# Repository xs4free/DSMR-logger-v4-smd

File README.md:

# DSMR-logger-v4.5

Reverse enginered version of [Willem aan de Wiel](https://github.com/mrWheel)'s excellent [DSMR-logger version 4.5](https://opencircuit.nl/Product/Slimme-meter-uitlezer-V4.5-Geassembleerd) to fit certain components I had lying around. The latest details he published are of the 4.0 version, detailed in [this blog](https://willem.aandewiel.nl/index.php/2019/04/09/dsmr-logger-v4-slimme-meter-uitlezer/).

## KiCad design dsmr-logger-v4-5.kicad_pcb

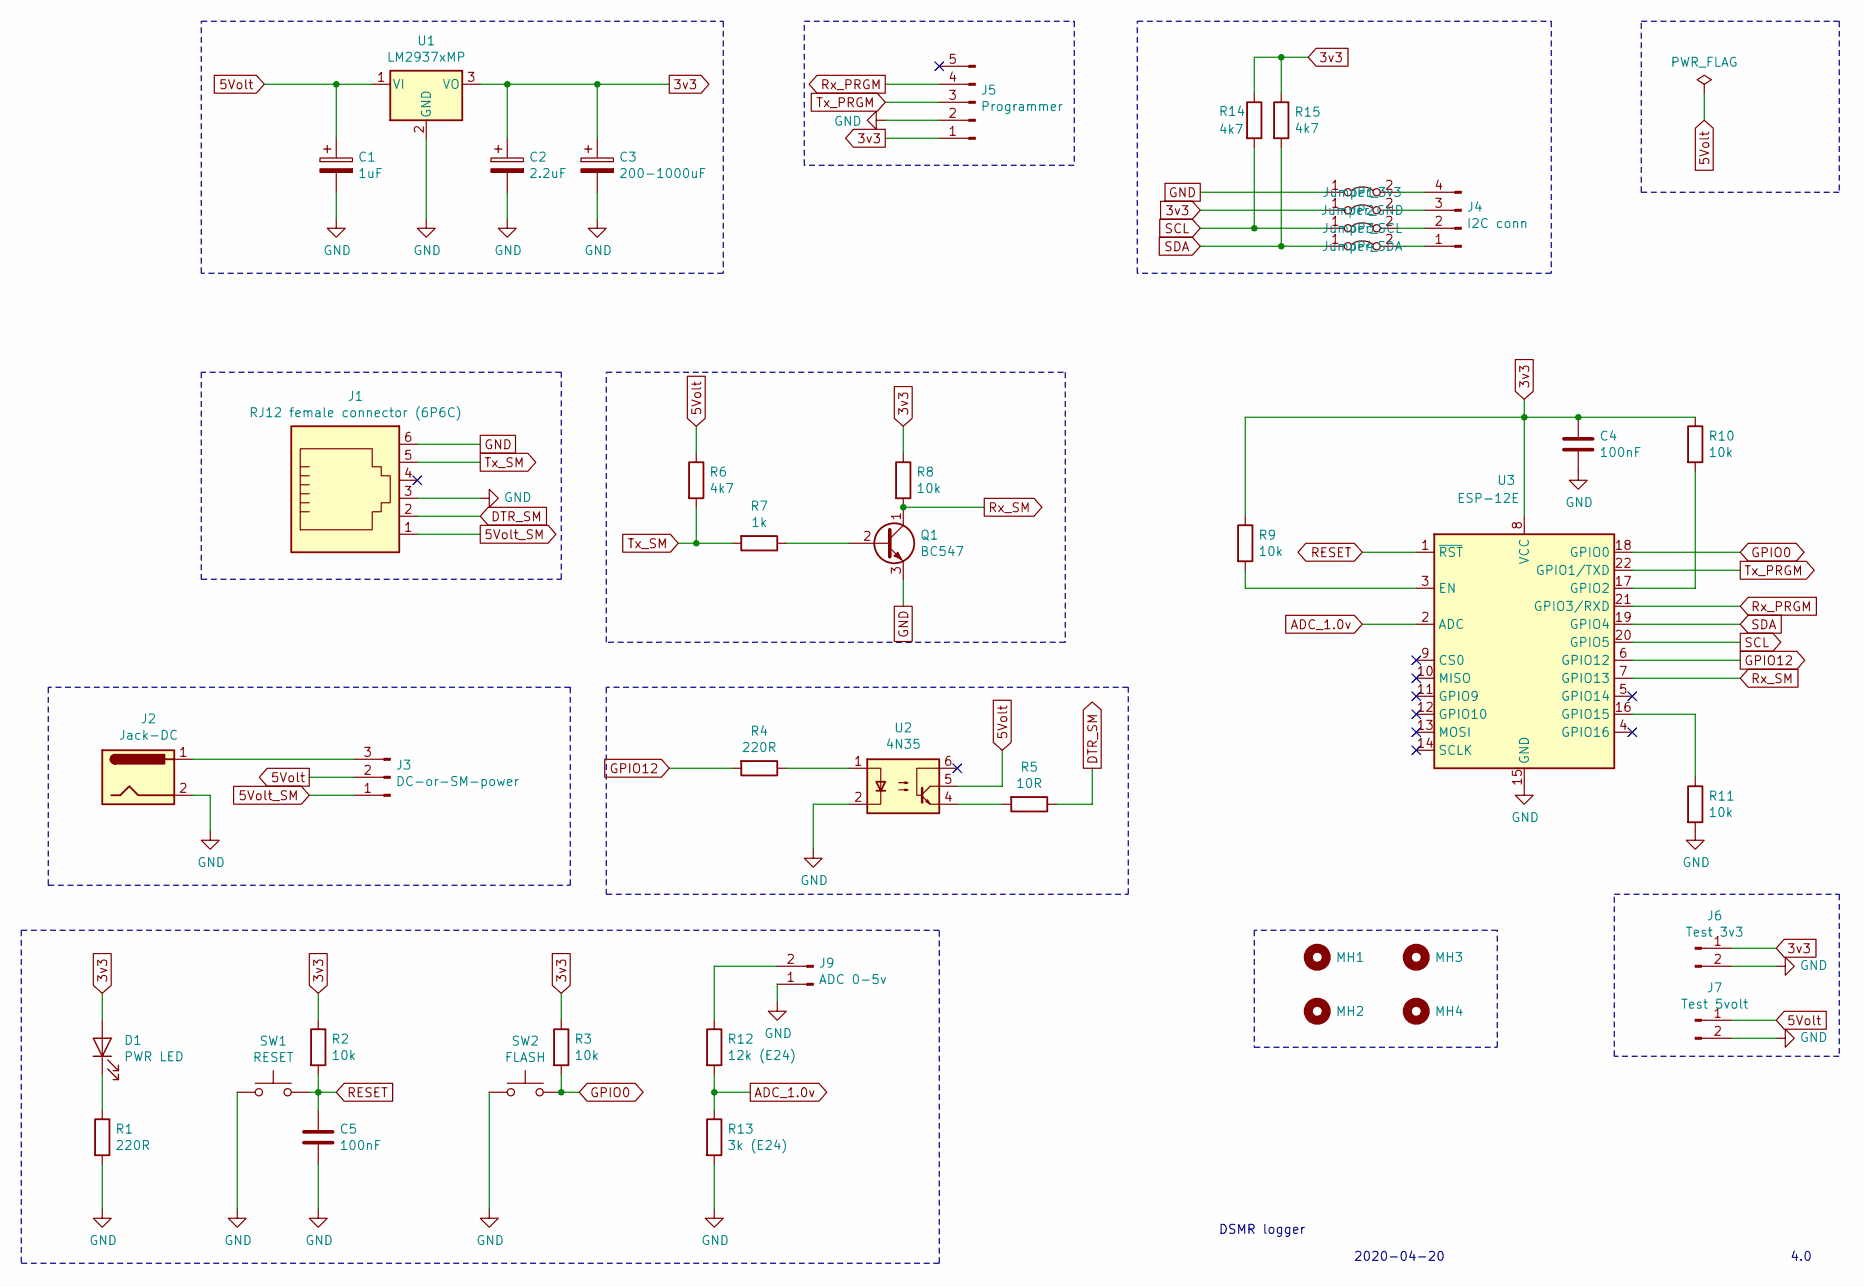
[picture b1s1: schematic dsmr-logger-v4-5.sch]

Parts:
C1: 1uF; CP_Radial_D5.0mm_P2.00mm
C2: 2.2uF; CP_Radial_D5.0mm_P2.00mm
C3: 200-1000uF; CP_Radial_D8.0mm_P5.00mm
C4, C5: 100nF; C_Disc_D5.0mm_W2.5mm_P5.00mm
D1: PWR LED; LED_D3.0mm
J1: RJ12 female connector (6P6C); RJ11-6
J2: Jack-DC; BarrelJack_CUI_PJ-102AH_Horizontal
J3: DC-or-SM-power; PinHeader_1x03_P2.54mm_Vertical
J4: I2C conn; PinSocket_1x04_P2.54mm_Vertical
J5: Programmer; PinHeader_1x05_P2.54mm_Vertical
J6: Test 3v3; PinHeader_1x02_P2.54mm_Vertical
J7: Test 5volt; PinHeader_1x02_P2.54mm_Vertical
J9: ADC 0-5v; PinHeader_1x02_P2.54mm_Vertical
JP1: Jumper_3v3; SolderJumper-2_P1.3mm_Bridged_Pad1.0x1.5mm
JP2: Jumper_GND; SolderJumper-2_P1.3mm_Bridged_Pad1.0x1.5mm
JP3: Jumper_SCL; SolderJumper-2_P1.3mm_Bridged_Pad1.0x1.5mm
JP4: Jumper_SDA; SolderJumper-2_P1.3mm_Bridged_Pad1.0x1.5mm
MH1, MH2, MH3, MH4: MountingHole; MountingHole_2.7mm_M2.5_DIN965
Q1: BC547; TO-92
R1, R4: 220R; R_Axial_DIN0207_L6.3mm_D2.5mm_P7.62mm_Horizontal
R2, R3, R8, R9, R10, R11: 10k; R_Axial_DIN0207_L6.3mm_D2.5mm_P7.62mm_Horizontal
R5: 10R; R_Axial_DIN0207_L6.3mm_D2.5mm_P7.62mm_Horizontal
R6, R14, R15: 4k7; R_Axial_DIN0207_L6.3mm_D2.5mm_P7.62mm_Horizontal
R7: 1k; R_Axial_DIN0207_L6.3mm_D2.5mm_P7.62mm_Horizontal
R12: 12k (E24); R_Axial_DIN0207_L6.3mm_D2.5mm_P7.62mm_Horizontal
R13: 3k (E24); R_Axial_DIN0207_L6.3mm_D2.5mm_P7.62mm_Horizontal
SW1: RESET; SW_PUSH_6mm_H7.3mm
SW2: FLASH; SW_PUSH_6mm_H13mm
U1: LM2937xMP; SOT-223-3_TabPin2
U2: 4N35; DIP-6_W7.62mm
U3: ESP-12E

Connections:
3v3: C2.1, C3.1, C4.1, D1.2 (A), J5.1, J6.1, JP2.1 (A), R2.1, R3.1, R8.1, R9.1, R10.1, R14.1, R15.1, U1.3 (VO), U3.8 (VCC)
5Volt: C1.1, J3.2, J7.1, R6.1, U1.1 (VI), U2.5
5Volt_SM: J1.1, J3.1
ADC_1.0v: R12.2, R13.1, U3.2 (ADC)
DTR_SM: J1.2, R5.1
GND: C1.2, C2.2, C3.2, C4.2, C5.2, J1.3, J1.6, J2.2, J5.2, J6.2, J7.2, J9.1, JP1.1 (A), Q1.3 (E), R1.2, R11.2, R13.2, SW1.1, SW2.1, U1.2 (GND), U2.2, U3.15 (GND)
GPIO0: R3.2, SW2.2, U3.18 (GPIO0)
GPIO12: R4.2, U3.6 (GPIO12)
unnamed: D1.1 (K), R1.1
unnamed: J2.1, J3.3
unnamed: J4.1, JP4.2 (B)
unnamed: J4.2, JP3.2 (B)
unnamed: J4.3, JP2.2 (B)
unnamed: J4.4, JP1.2 (B)
unnamed: J9.2, R12.1
unnamed: Q1.2 (B), R7.1
unnamed: R4.1, U2.1
unnamed: R5.2, U2.4
unnamed: R9.2, U3.3 (EN)
unnamed: R10.2, U3.17 (GPIO2)
unnamed: R11.1, U3.16 (GPIO15)
RESET: C5.1, R2.2, SW1.2, U3.1 (~RST)
Rx_PRGM: J5.4, U3.21 (GPIO3/RXD)
Rx_SM: Q1.1 (C), R8.2, U3.7 (GPIO13)
SCL: JP3.1 (A), R14.2, U3.20 (GPIO5)
SDA: JP4.1 (A), R15.2, U3.19 (GPIO4)
Tx_PRGM: J5.3, U3.22 (GPIO1/TXD)
Tx_SM: J1.5, R6.2, R7.2

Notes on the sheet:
DSMR logger
4.0
2020-04-20

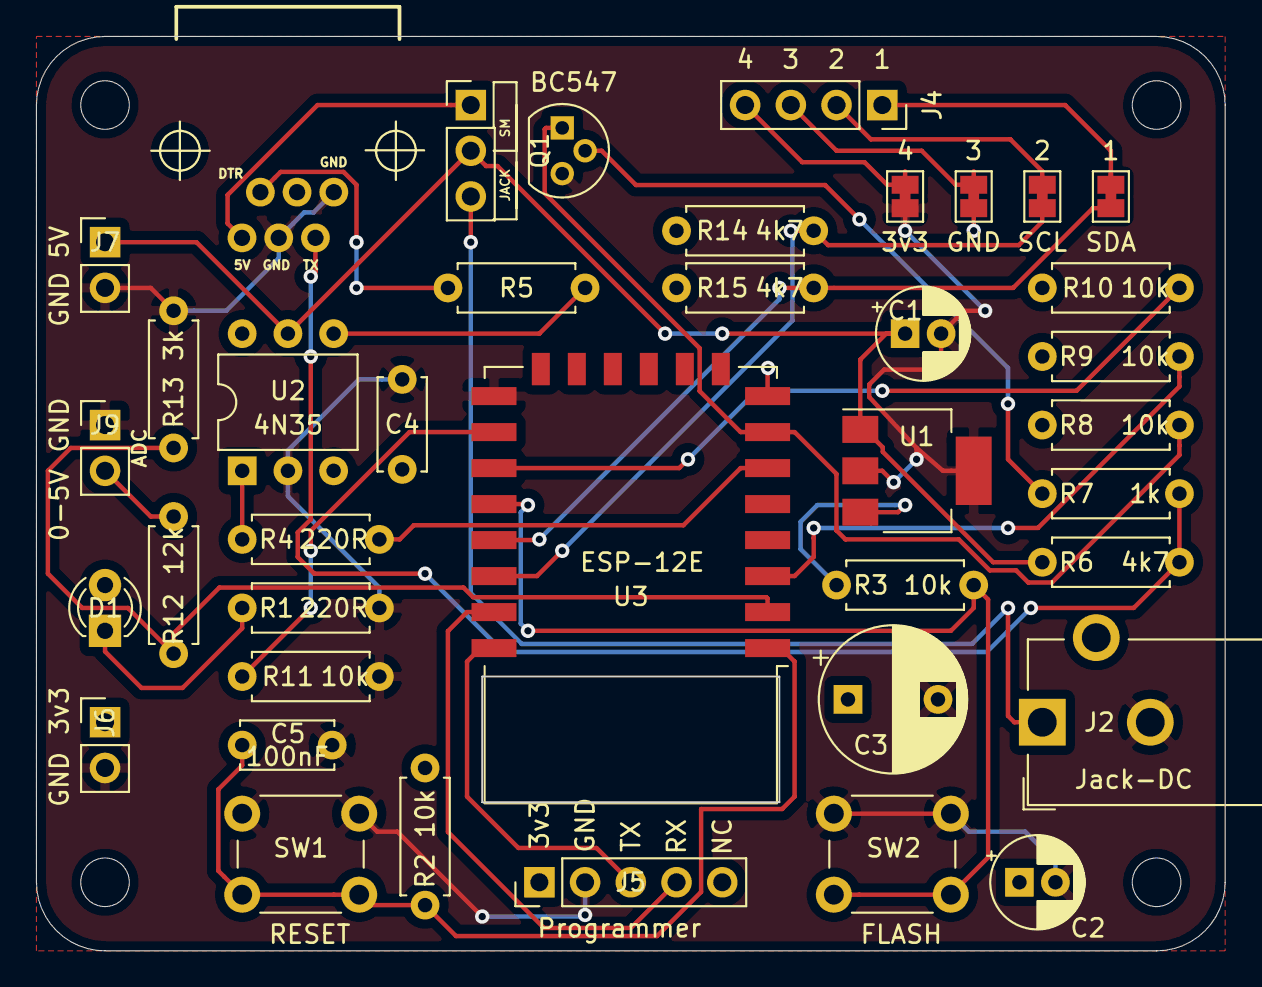
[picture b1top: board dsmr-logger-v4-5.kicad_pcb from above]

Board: 2 copper layers, 66.0 x 50.8 mm, 43 parts (0 on the bottom side), 28 nets.

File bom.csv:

"Source:"	"C:\Git\DSMR-logger-v4-smd\dsmr-logger-v4-5.sch"
"Date:"	"4/20/2020 11:20:06 PM"
"Tool:"	"Eeschema (5.1.5)-3"
"Component Count:"	"43"
"Ref"	"Value"	"Part"	"Footprint"	"Description"	"Vendor"
"C1"	"1uF"	"Device:CP"	"Capacitor_THT:CP_Radial_D5.0mm_P2.00mm"	"Polarized capacitor"	""
"C2"	"2.2uF"	"Device:CP"	"Capacitor_THT:CP_Radial_D5.0mm_P2.00mm"	"Polarized capacitor"	""
"C3"	"200-1000uF"	"Device:CP"	"Capacitor_THT:CP_Radial_D8.0mm_P5.00mm"	"Polarized capacitor"	""
"C4"	"100nF"	"Device:C"	"Capacitor_THT:C_Disc_D5.0mm_W2.5mm_P5.00mm"	"Unpolarized capacitor"	""
"C5"	"100nF"	"Device:C"	"Capacitor_THT:C_Disc_D5.0mm_W2.5mm_P5.00mm"	"Unpolarized capacitor"	""
"D1"	"PWR LED"	"Device:LED"	"LED_THT:LED_D3.0mm"	"Light emitting diode"	""
"J1"	"RJ12 female connector (6P6C)"	"Connector:6P6C"	"Connectors-P1:RJ11-6"	"RJ connector, 6P6C (6 positions 6 connected), RJ12/RJ18/RJ25"	""
"J2"	"Jack-DC"	"Connector:Jack-DC"	"Connector_BarrelJack:BarrelJack_CUI_PJ-102AH_Horizontal"	"DC Barrel Jack"	""
"J3"	"DC-or-SM-power"	"Connector:Conn_01x03_Male"	"Connector_PinHeader_2.54mm:PinHeader_1x03_P2.54mm_Vertical"	"Generic connector, single row, 01x03, script generated (kicad-library-utils/schlib/autogen/connector/)"	""
"J4"	"I2C conn"	"Connector:Conn_01x04_Male"	"Connector_PinSocket_2.54mm:PinSocket_1x04_P2.54mm_Vertical"	"Generic connector, single row, 01x04, script generated (kicad-library-utils/schlib/autogen/connector/)"	""
"J5"	"Programmer"	"Connector:Conn_01x05_Male"	"Connector_PinHeader_2.54mm:PinHeader_1x05_P2.54mm_Vertical"	"Generic connector, single row, 01x05, script generated (kicad-library-utils/schlib/autogen/connector/)"	""
"J6"	"Test 3v3"	"Connector:Conn_01x02_Male"	"Connector_PinHeader_2.54mm:PinHeader_1x02_P2.54mm_Vertical"	"Generic connector, single row, 01x02, script generated (kicad-library-utils/schlib/autogen/connector/)"	""
"J7"	"Test 5volt"	"Connector:Conn_01x02_Male"	"Connector_PinHeader_2.54mm:PinHeader_1x02_P2.54mm_Vertical"	"Generic connector, single row, 01x02, script generated (kicad-library-utils/schlib/autogen/connector/)"	""
"J9"	"ADC 0-5v"	"Connector:Conn_01x02_Male"	"Connector_PinHeader_2.54mm:PinHeader_1x02_P2.54mm_Vertical"	"Generic connector, single row, 01x02, script generated (kicad-library-utils/schlib/autogen/connector/)"	""
"JP1"	"Jumper_3v3"	"Jumper:Jumper_2_Bridged"	"Jumper:SolderJumper-2_P1.3mm_Bridged_Pad1.0x1.5mm"	"Jumper, 2-pole, closed/bridged"	""
"JP2"	"Jumper_GND"	"Jumper:Jumper_2_Bridged"	"Jumper:SolderJumper-2_P1.3mm_Bridged_Pad1.0x1.5mm"	"Jumper, 2-pole, closed/bridged"	""
"JP3"	"Jumper_SCL"	"Jumper:Jumper_2_Bridged"	"Jumper:SolderJumper-2_P1.3mm_Bridged_Pad1.0x1.5mm"	"Jumper, 2-pole, closed/bridged"	""
"JP4"	"Jumper_SDA"	"Jumper:Jumper_2_Bridged"	"Jumper:SolderJumper-2_P1.3mm_Bridged_Pad1.0x1.5mm"	"Jumper, 2-pole, closed/bridged"	""
"MH1"	"MountingHole"	"Mechanical:MountingHole"	"MountingHole:MountingHole_2.7mm_M2.5_DIN965"	"Mounting Hole without connection"	""
"MH2"	"MountingHole"	"Mechanical:MountingHole"	"MountingHole:MountingHole_2.7mm_M2.5_DIN965"	"Mounting Hole without connection"	""
"MH3"	"MountingHole"	"Mechanical:MountingHole"	"MountingHole:MountingHole_2.7mm_M2.5_DIN965"	"Mounting Hole without connection"	""
"MH4"	"MountingHole"	"Mechanical:MountingHole"	"MountingHole:MountingHole_2.7mm_M2.5_DIN965"	"Mounting Hole without connection"	""
"Q1"	"BC547"	"Transistor_BJT:BC547"	"Package_TO_SOT_THT:TO-92"	"0.1A Ic, 45V Vce, Small Signal NPN Transistor, TO-92"	""
"R1"	"220R"	"Device:R"	"Resistor_THT:R_Axial_DIN0207_L6.3mm_D2.5mm_P7.62mm_Horizontal"	"Resistor"	""
"R2"	"10k"	"Device:R"	"Resistor_THT:R_Axial_DIN0207_L6.3mm_D2.5mm_P7.62mm_Horizontal"	"Resistor"	""
"R3"	"10k"	"Device:R"	"Resistor_THT:R_Axial_DIN0207_L6.3mm_D2.5mm_P7.62mm_Horizontal"	"Resistor"	""
"R4"	"220R"	"Device:R"	"Resistor_THT:R_Axial_DIN0207_L6.3mm_D2.5mm_P7.62mm_Horizontal"	"Resistor"	""
"R5"	"10R"	"Device:R"	"Resistor_THT:R_Axial_DIN0207_L6.3mm_D2.5mm_P7.62mm_Horizontal"	"Resistor"	""
"R6"	"4k7"	"Device:R"	"Resistor_THT:R_Axial_DIN0207_L6.3mm_D2.5mm_P7.62mm_Horizontal"	"Resistor"	""
"R7"	"1k"	"Device:R"	"Resistor_THT:R_Axial_DIN0207_L6.3mm_D2.5mm_P7.62mm_Horizontal"	"Resistor"	""
"R8"	"10k"	"Device:R"	"Resistor_THT:R_Axial_DIN0207_L6.3mm_D2.5mm_P7.62mm_Horizontal"	"Resistor"	""
"R9"	"10k"	"Device:R"	"Resistor_THT:R_Axial_DIN0207_L6.3mm_D2.5mm_P7.62mm_Horizontal"	"Resistor"	""
"R10"	"10k"	"Device:R"	"Resistor_THT:R_Axial_DIN0207_L6.3mm_D2.5mm_P7.62mm_Horizontal"	"Resistor"	""
"R11"	"10k"	"Device:R"	"Resistor_THT:R_Axial_DIN0207_L6.3mm_D2.5mm_P7.62mm_Horizontal"	"Resistor"	""
"R12"	"12k (E24)"	"Device:R"	"Resistor_THT:R_Axial_DIN0207_L6.3mm_D2.5mm_P7.62mm_Horizontal"	"Resistor"	""
"R13"	"3k (E24)"	"Device:R"	"Resistor_THT:R_Axial_DIN0207_L6.3mm_D2.5mm_P7.62mm_Horizontal"	"Resistor"	""
"R14"	"4k7"	"Device:R"	"Resistor_THT:R_Axial_DIN0207_L6.3mm_D2.5mm_P7.62mm_Horizontal"	"Resistor"	""
"R15"	"4k7"	"Device:R"	"Resistor_THT:R_Axial_DIN0207_L6.3mm_D2.5mm_P7.62mm_Horizontal"	"Resistor"	""
"SW1"	"RESET"	"Switch:SW_Push"	"Button_Switch_THT:SW_PUSH_6mm_H7.3mm"	"Push button switch, generic, two pins"	""
"SW2"	"FLASH"	"Switch:SW_Push"	"Button_Switch_THT:SW_PUSH_6mm_H13mm"	"Push button switch, generic, two pins"	""
"U1"	"LM2937xMP"	"Regulator_Linear:LM2937xMP"	"Package_TO_SOT_SMD:SOT-223-3_TabPin2"	"500-mA Low Dropout Regulator, SOT-223"	""
"U2"	"4N35"	"Isolator:4N35"	"Package_DIP:DIP-6_W7.62mm"	"Optocoupler, Phototransistor Output, with Base Connection, Vce 70V, CTR 100%, Viso 5000V, DIP6"	""
"U3"	"ESP-12E"	"RF_Module:ESP-12E"	"RF_Module:ESP-12E"	"802.11 b/g/n Wi-Fi Module"	""

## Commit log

2019-06-30 Added images from willem.aandewiel.nl as reference for schema
2019-12-28 Add first schema and more images
2019-12-28 Fixed hyperlinks
2019-12-31 Add pcb layout
2020-04-20 Silk mask updated, changed JP4, added 3D renders
